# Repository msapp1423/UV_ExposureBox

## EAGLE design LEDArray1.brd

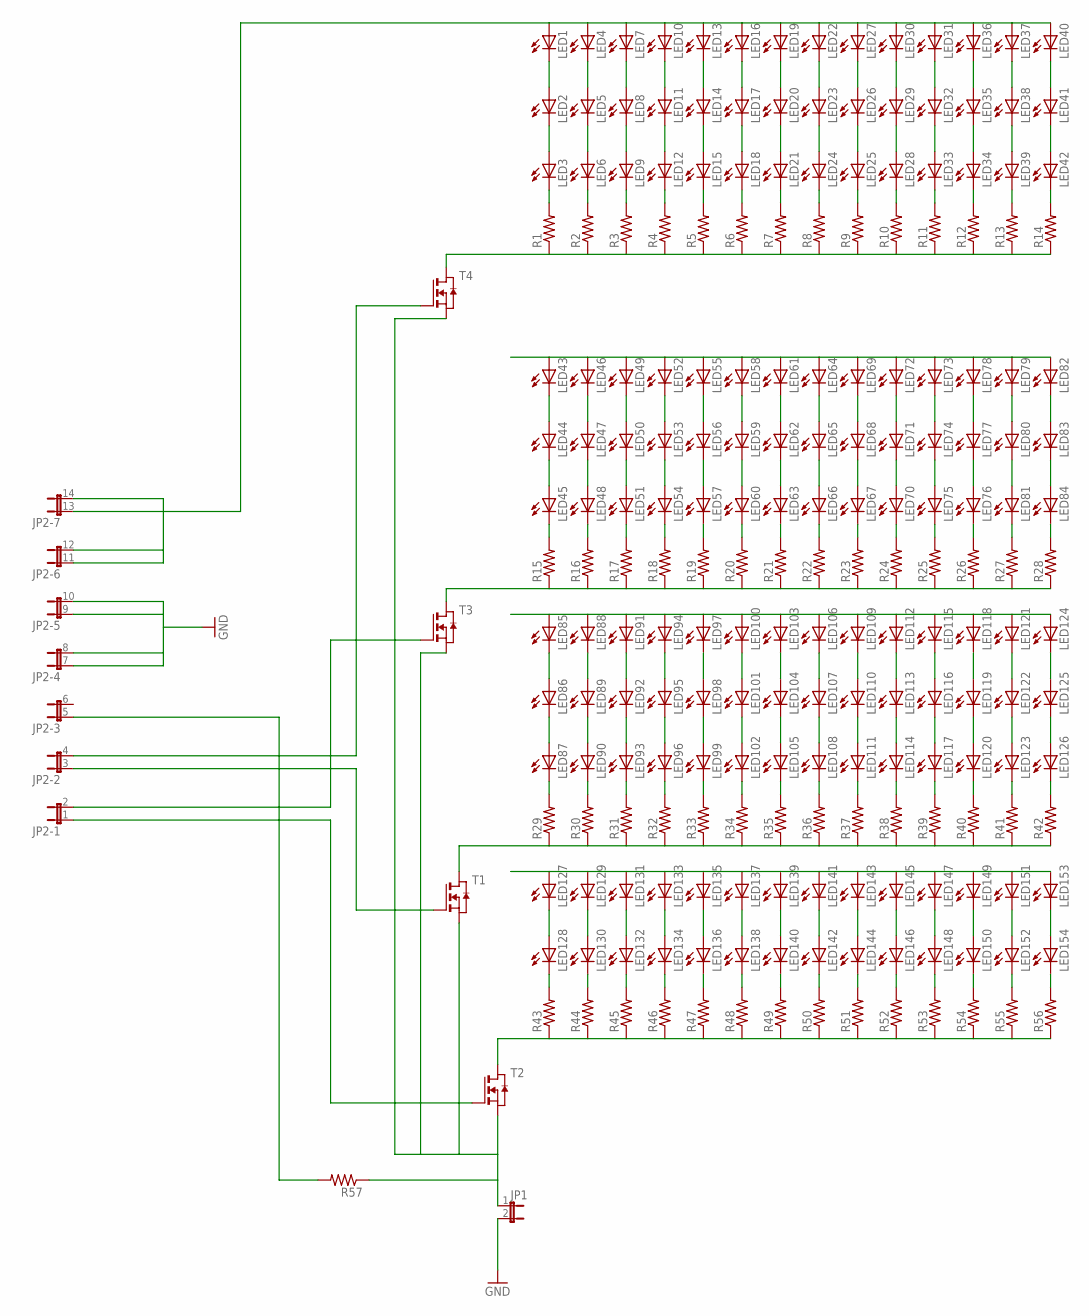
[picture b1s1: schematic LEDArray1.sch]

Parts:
JP1: JP1E; JP1
JP2: JP7QE; JP7Q
LED1, LED2, LED3, LED4, LED5, LED6, LED7, LED8, LED9, LED10, LED11, LED12, LED13, LED14, LED15, LED16, LED17, LED18, LED19, LED20, LED21, LED22, LED23, LED24, LED25, LED26, LED27, LED28, LED29, LED30, LED31, LED32, LED33, LED34, LED35, LED36, LED37, LED38, LED39, LED40, LED41, LED42, LED43, LED44, LED45, LED46, LED47, LED48, LED49, LED50, LED51, LED52, LED53, LED54, LED55, LED56, LED57, LED58, LED59, LED60, LED61, LED62, LED63, LED64, LED65, LED66, LED67, LED68, LED69, LED70, LED71, LED72, LED73, LED74, LED75, LED76, LED77, LED78, LED79, LED80, LED81, LED82, LED83, LED84, LED85, LED86, LED87, LED88, LED89, LED90, LED91, LED92, LED93, LED94, LED95, LED96, LED97, LED98, LED99, LED100, LED101, LED102, LED103, LED104, LED105, LED106, LED107, LED108, LED109, LED110, LED111, LED112, LED113, LED114, LED115, LED116, LED117, LED118, LED119, LED120, LED121, LED122, LED123, LED124, LED125, LED126, LED127, LED128, LED129, LED130, LED131, LED132, LED133, LED134, LED135, LED136, LED137, LED138, LED139, LED140, LED141, LED142, LED143, LED144, LED145, LED146, LED147, LED148, LED149, LED150, LED151, LED152, LED153, LED154: LED5MM
R1, R2, R3, R4, R5, R6, R7, R8, R9, R10, R11, R12, R13, R14, R15, R16, R17, R18, R19, R20, R21, R22, R23, R24, R25, R26, R27, R28, R29, R30, R31, R32, R33, R34, R35, R36, R37, R38, R39, R40, R41, R42, R43, R44, R45, R46, R47, R48, R49, R50, R51, R52, R53, R54, R55, R56, R57: R-US_R0805; R0805
T1, T2, T3, T4: NMOSSOT23; SOT-23

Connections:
GND: JP1.2, JP2.7 (1), JP2.8 (2), JP2.9 (1), JP2.10 (2)
unnamed: LED1.K (C), LED2.A
unnamed: LED4.K (C), LED5.A
unnamed: LED7.K (C), LED8.A
unnamed: LED10.K (C), LED11.A
unnamed: LED13.K (C), LED14.A
unnamed: LED16.K (C), LED17.A
unnamed: LED19.K (C), LED20.A
unnamed: LED22.K (C), LED23.A
unnamed: LED26.A, LED27.K (C)
unnamed: LED29.A, LED30.K (C)
unnamed: LED31.K (C), LED32.A
unnamed: LED35.A, LED36.K (C)
unnamed: LED37.K (C), LED38.A
unnamed: LED40.K (C), LED41.A
unnamed: LED41.K (C), LED42.A
unnamed: LED38.K (C), LED39.A
unnamed: LED34.A, LED35.K (C)
unnamed: LED32.K (C), LED33.A
unnamed: LED28.A, LED29.K (C)
unnamed: LED25.A, LED26.K (C)
unnamed: LED23.K (C), LED24.A
unnamed: LED20.K (C), LED21.A
unnamed: LED17.K (C), LED18.A
unnamed: LED14.K (C), LED15.A
unnamed: LED11.K (C), LED12.A
unnamed: LED8.K (C), LED9.A
unnamed: LED5.K (C), LED6.A
unnamed: LED2.K (C), LED3.A
unnamed: R1.1, R2.1, R3.1, R4.1, R5.1, R6.1, R7.1, R8.1, R9.1, R10.1, R11.1, R12.1, R13.1, R14.1, T4.1 (D)
unnamed: LED43.K (C), LED44.A
unnamed: LED46.K (C), LED47.A
unnamed: LED49.K (C), LED50.A
unnamed: LED52.K (C), LED53.A
unnamed: LED55.K (C), LED56.A
unnamed: LED58.K (C), LED59.A
unnamed: LED61.K (C), LED62.A
unnamed: LED64.K (C), LED65.A
unnamed: LED68.A, LED69.K (C)
unnamed: LED71.A, LED72.K (C)
unnamed: LED73.K (C), LED74.A
unnamed: LED77.A, LED78.K (C)
unnamed: LED79.K (C), LED80.A
unnamed: LED82.K (C), LED83.A
unnamed: LED83.K (C), LED84.A
unnamed: LED80.K (C), LED81.A
unnamed: LED76.A, LED77.K (C)
unnamed: LED74.K (C), LED75.A
unnamed: LED70.A, LED71.K (C)
unnamed: LED67.A, LED68.K (C)
unnamed: LED65.K (C), LED66.A
unnamed: LED62.K (C), LED63.A
unnamed: LED59.K (C), LED60.A
unnamed: LED56.K (C), LED57.A
unnamed: LED53.K (C), LED54.A
unnamed: LED50.K (C), LED51.A
unnamed: LED47.K (C), LED48.A
unnamed: LED44.K (C), LED45.A
unnamed: R15.1, R16.1, R17.1, R18.1, R19.1, R20.1, R21.1, R22.1, R23.1, R24.1, R25.1, R26.1, R27.1, R28.1, T3.1 (D)
unnamed: LED85.K (C), LED86.A
unnamed: LED86.K (C), LED87.A
unnamed: LED88.K (C), LED89.A
unnamed: LED91.K (C), LED92.A
unnamed: LED94.K (C), LED95.A
unnamed: LED97.K (C), LED98.A
unnamed: LED100.K (C), LED101.A
unnamed: LED103.K (C), LED104.A
unnamed: LED106.K (C), LED107.A
unnamed: LED109.K (C), LED110.A
unnamed: LED112.K (C), LED113.A
unnamed: LED115.K (C), LED116.A
unnamed: LED118.K (C), LED119.A
unnamed: LED121.K (C), LED122.A
unnamed: LED124.K (C), LED125.A
unnamed: LED125.K (C), LED126.A
unnamed: LED122.K (C), LED123.A
unnamed: LED119.K (C), LED120.A
unnamed: LED116.K (C), LED117.A
unnamed: LED113.K (C), LED114.A
unnamed: LED110.K (C), LED111.A
unnamed: LED107.K (C), LED108.A
unnamed: LED104.K (C), LED105.A
unnamed: LED101.K (C), LED102.A
unnamed: LED98.K (C), LED99.A
unnamed: LED95.K (C), LED96.A
unnamed: LED92.K (C), LED93.A
unnamed: LED89.K (C), LED90.A
unnamed: R29.1, R30.1, R31.1, R32.1, R33.1, R34.1, R35.1, R36.1, R37.1, R38.1, R39.1, R40.1, R41.1, R42.1, T1.1 (D)
unnamed: LED127.K (C), LED128.A
unnamed: LED129.K (C), LED130.A
unnamed: LED131.K (C), LED132.A
unnamed: LED133.K (C), LED134.A
unnamed: LED135.K (C), LED136.A
unnamed: LED137.K (C), LED138.A
unnamed: LED139.K (C), LED140.A
unnamed: LED141.K (C), LED142.A
unnamed: LED143.K (C), LED144.A
unnamed: LED145.K (C), LED146.A
unnamed: LED147.K (C), LED148.A
unnamed: LED149.K (C), LED150.A
unnamed: LED151.K (C), LED152.A
unnamed: LED153.K (C), LED154.A
unnamed: R43.1, R44.1, R45.1, R46.1, R47.1, R48.1, R49.1, R50.1, R51.1, R52.1, R53.1, R54.1, R55.1, R56.1, T2.1 (D)
unnamed: JP2.3 (1), T1.3 (G)
unnamed: JP2.5 (1), R57.2
unnamed: LED42.K (C), R14.2
unnamed: LED39.K (C), R13.2
unnamed: LED34.K (C), R12.2
unnamed: LED33.K (C), R11.2
unnamed: LED28.K (C), R10.2
unnamed: LED25.K (C), R9.2
unnamed: LED24.K (C), R8.2
unnamed: LED21.K (C), R7.2
unnamed: LED18.K (C), R6.2
unnamed: LED15.K (C), R5.2
unnamed: LED12.K (C), R4.2
unnamed: LED9.K (C), R3.2
unnamed: LED6.K (C), R2.2
unnamed: LED3.K (C), R1.2
unnamed: LED45.K (C), R15.2
unnamed: LED48.K (C), R16.2
unnamed: LED51.K (C), R17.2
unnamed: LED54.K (C), R18.2
unnamed: LED57.K (C), R19.2
unnamed: LED60.K (C), R20.2
unnamed: LED63.K (C), R21.2
unnamed: LED66.K (C), R22.2
unnamed: LED67.K (C), R23.2
unnamed: LED70.K (C), R24.2
unnamed: LED75.K (C), R25.2
unnamed: LED76.K (C), R26.2
unnamed: LED81.K (C), R27.2
unnamed: LED84.K (C), R28.2
unnamed: LED87.K (C), R29.2
unnamed: LED90.K (C), R30.2
unnamed: LED93.K (C), R31.2
unnamed: LED96.K (C), R32.2
unnamed: LED99.K (C), R33.2
unnamed: LED102.K (C), R34.2
unnamed: LED105.K (C), R35.2
unnamed: LED108.K (C), R36.2
unnamed: LED111.K (C), R37.2
unnamed: LED114.K (C), R38.2
unnamed: LED117.K (C), R39.2
unnamed: LED120.K (C), R40.2
unnamed: LED123.K (C), R41.2
unnamed: LED126.K (C), R42.2
unnamed: LED128.K (C), R43.2
unnamed: LED130.K (C), R44.2
unnamed: LED132.K (C), R45.2
unnamed: LED134.K (C), R46.2
unnamed: LED136.K (C), R47.2
unnamed: LED138.K (C), R48.2
unnamed: LED140.K (C), R49.2
unnamed: LED142.K (C), R50.2
unnamed: LED144.K (C), R51.2
unnamed: LED146.K (C), R52.2
unnamed: LED148.K (C), R53.2
unnamed: LED150.K (C), R54.2
unnamed: LED152.K (C), R55.2
unnamed: LED154.K (C), R56.2
unnamed: JP2.1, T2.3 (G)
unnamed: JP1.1, R57.1, T1.2 (S), T2.2 (S), T3.2 (S), T4.2 (S)
unnamed: JP2.2, T3.3 (G)
unnamed: JP2.4 (2), T4.3 (G)
VCC: JP2.11 (1), JP2.12 (2), JP2.13 (1), JP2.14 (2), LED1.A, LED4.A, LED7.A, LED10.A, LED13.A, LED16.A, LED19.A, LED22.A, LED27.A, LED30.A, LED31.A, LED36.A, LED37.A, LED40.A, LED43.A, LED46.A, LED49.A, LED52.A, LED55.A, LED58.A, LED61.A, LED64.A, LED69.A, LED72.A, LED73.A, LED78.A, LED79.A, LED82.A, LED85.A, LED88.A, LED91.A, LED94.A, LED97.A, LED100.A, LED103.A, LED106.A, LED109.A, LED112.A, LED115.A, LED118.A, LED121.A, LED124.A, LED127.A, LED129.A, LED131.A, LED133.A, LED135.A, LED137.A, LED139.A, LED141.A, LED143.A, LED145.A, LED147.A, LED149.A, LED151.A, LED153.A

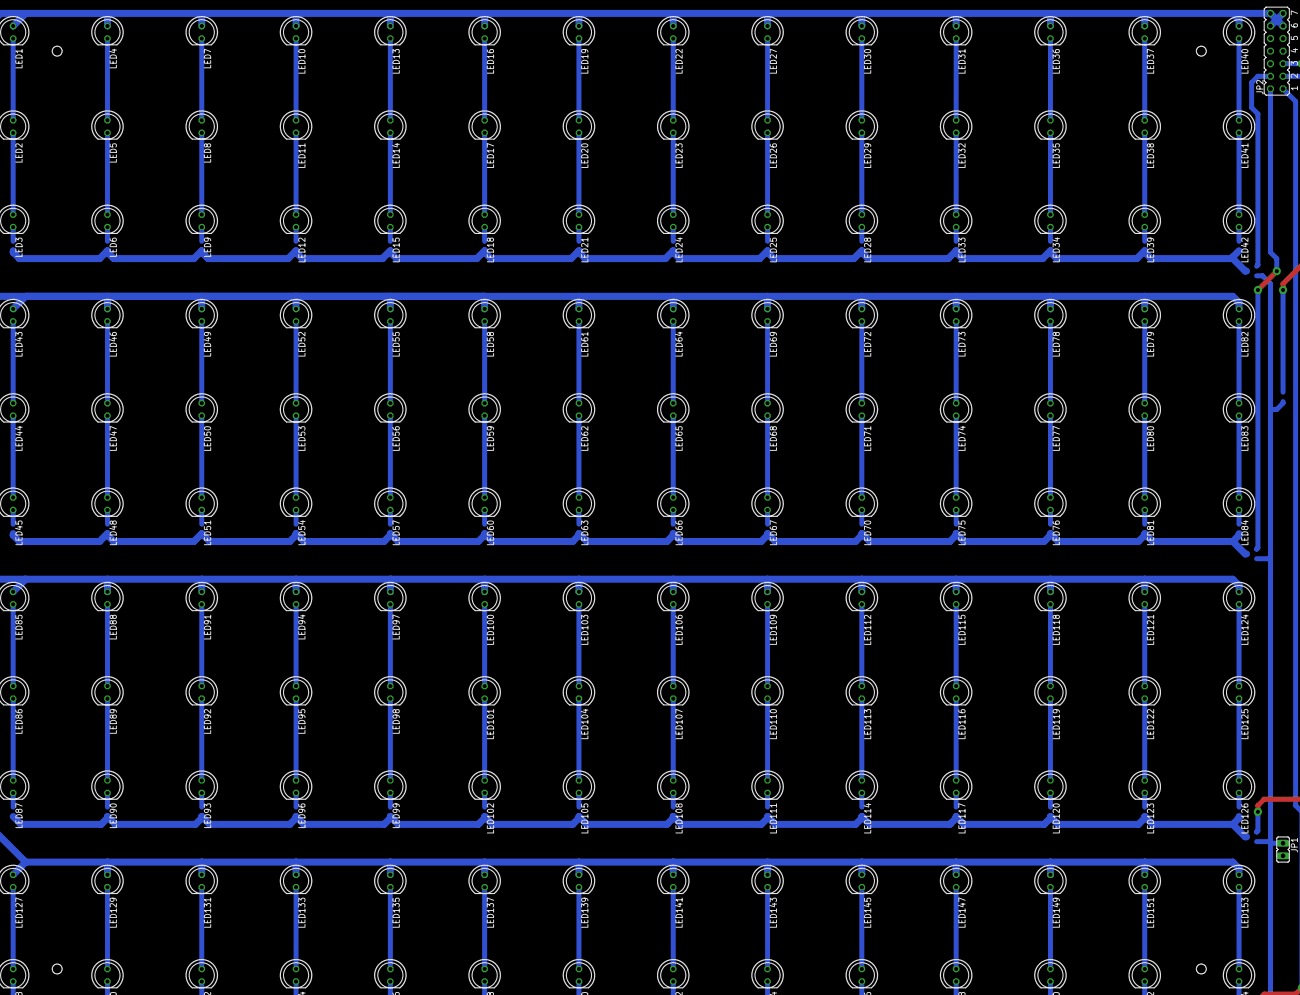
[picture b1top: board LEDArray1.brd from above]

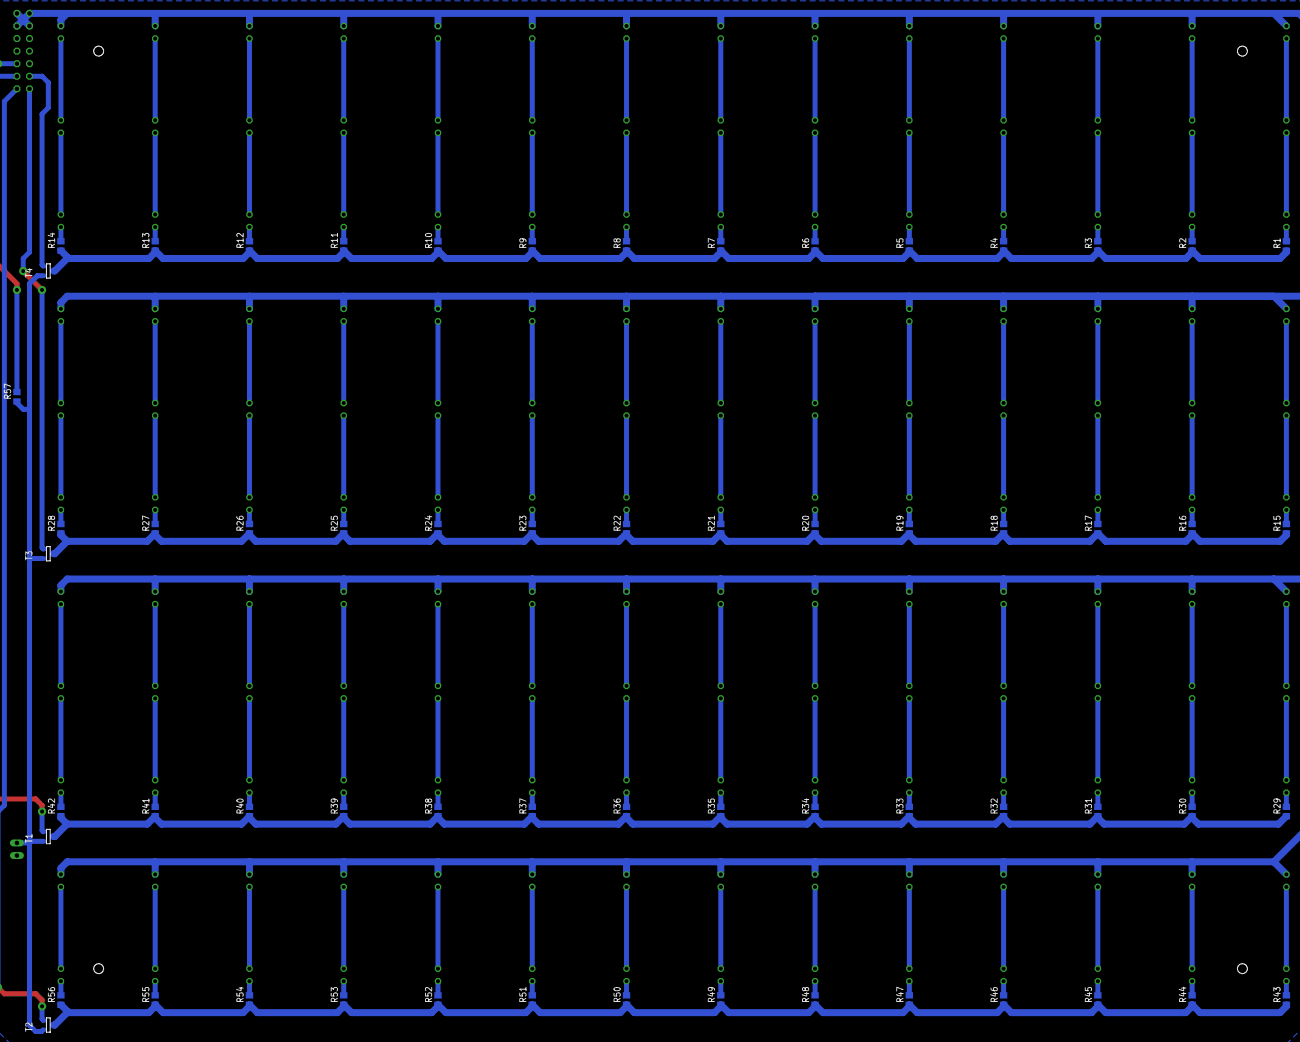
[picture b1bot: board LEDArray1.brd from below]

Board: 2 copper layers, 217 parts (61 on the bottom side), 166 nets.
